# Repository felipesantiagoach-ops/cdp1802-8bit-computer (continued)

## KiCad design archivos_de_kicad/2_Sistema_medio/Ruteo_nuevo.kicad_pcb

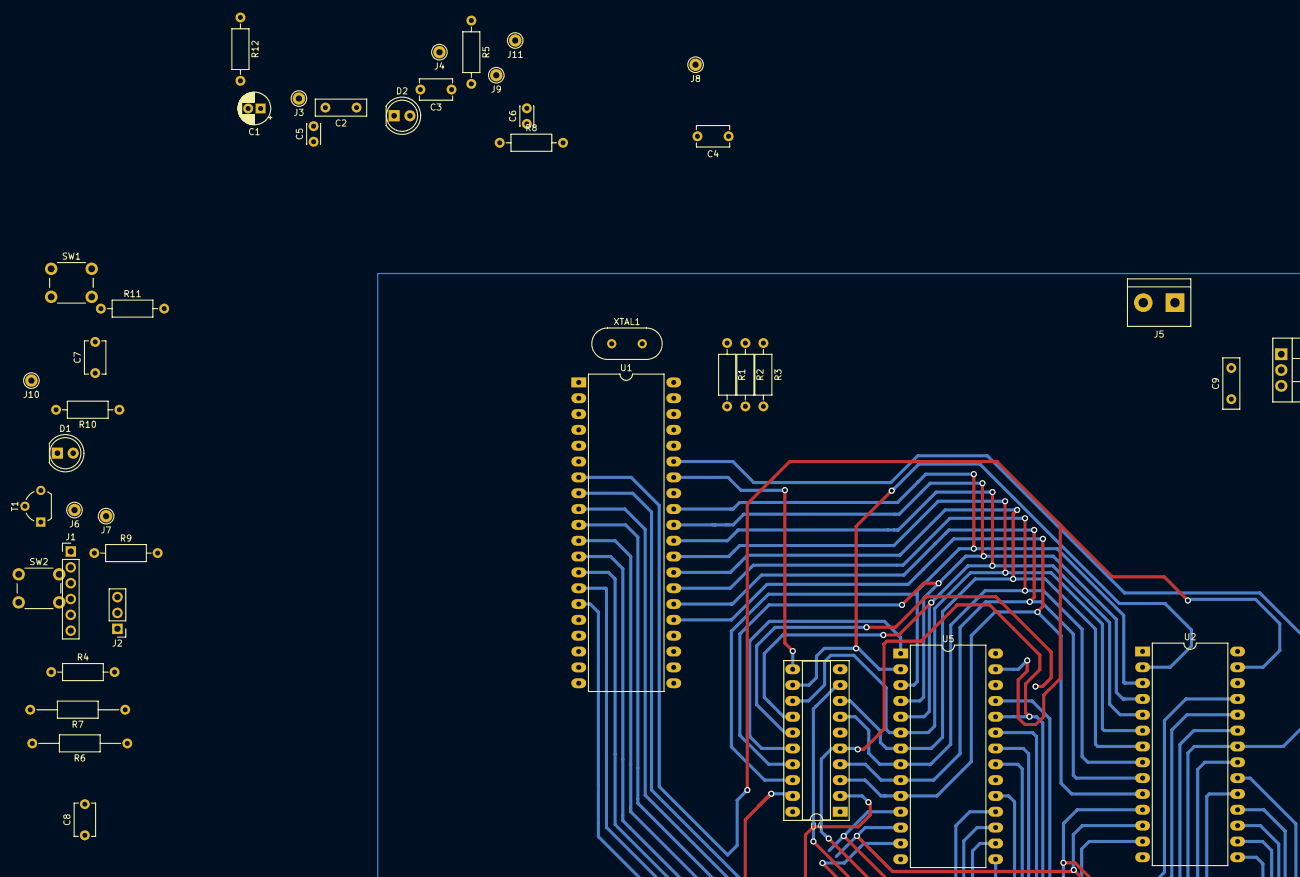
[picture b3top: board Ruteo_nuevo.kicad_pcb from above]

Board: 2 copper layers, 43 parts (0 on the bottom side), 50 nets.

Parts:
C1: 10uF; CP_Radial_D5.0mm_P2.00mm
C2, C9: 0,1uF; C_Disc_D8.0mm_W2.5mm_P5.00mm
C3, C4, C7, C8: 0,1uF; C_Disc_D5.1mm_W3.2mm_P5.00mm
C5, C6: 30pF; C_Disc_D3.0mm_W2.0mm_P2.50mm
D1, D2: LD271; LED_D5.0mm
J1: Conn_01x06_Male; PinHeader_1x06_P2.54mm_Vertical
J2: N1,2,3; PinHeader_1x03_P2.54mm_Vertical
J3, J4, J6, J7, J8: 1; Pin_D1.0mm_L10.0mm
J5: Voltaje de entrada; TerminalBlock_bornier-2_P5.08mm
J9: 2; Pin_D1.0mm_L10.0mm
J10: 3; Pin_D1.0mm_L10.0mm
J11: 4; Pin_D1.0mm_L10.0mm
R1, R2, R3: 47K; R_Axial_DIN0207_L6.3mm_D2.5mm_P10.16mm_Horizontal
R4, R11, R12: 47k; R_Axial_DIN0207_L6.3mm_D2.5mm_P10.16mm_Horizontal
R5, R9: 220; R_Axial_DIN0207_L6.3mm_D2.5mm_P10.16mm_Horizontal
R6, R7: 47K; R_Axial_DIN0207_L6.3mm_D2.5mm_P15.24mm_Horizontal
R8: 10M; R_Axial_DIN0207_L6.3mm_D2.5mm_P10.16mm_Horizontal
R10: 10K; R_Axial_DIN0207_L6.3mm_D2.5mm_P10.16mm_Horizontal
SW1, SW2: SW_Push; SW_PUSH_6mm_H4.3mm
T1: PN2222A; TO-92L_Wide
U1: CDP1802ACE; DIP-40_W15.24mm_LongPads
U2: EEPROM; DIP-28_W15.24mm_LongPads
U3: L7805; TO-220-3_Vertical
U4: 74LS373; DIP-20_W7.62mm_Socket_LongPads
U5: Dallas_RAM; DIP-28_W15.24mm_LongPads
XTAL1: 4 MHz; Crystal_HC18-U_Vertical

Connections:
A0: U1.25 (MA0), U2.10 (A0), U4.3 (D0), U5.10 (A0)
A1: U1.26 (MA1), U2.9 (A1), U4.4 (D1), U5.9 (A1)
A2: U1.27 (MA2), U2.8 (A2), U4.7 (D2), U5.8 (A2)
A3: U1.28 (MA3), U2.7 (A3), U4.8 (D3), U5.7 (A3)
A4: U1.29 (MA4), U2.6 (A4), U4.13 (D4), U5.6 (A4)
A5: U1.30 (MA5), U2.5 (A5), U4.14 (D5), U5.5 (A5)
A6: U1.31 (MA6), U2.4 (A6), U4.17 (D6), U5.4 (A6)
A7: U1.32 (MA7), U2.3 (A7), U4.18 (D7), U5.3 (A7)
A8: U2.25 (A8), U4.2 (O0), U5.25 (A8)
A9: U2.24 (A9), U4.5 (O1), U5.24 (A9)
A10: U2.21 (A10), U4.6 (O2), U5.21 (A10)
A11: U2.23 (A11), U4.9 (O3), U5.23 (A11)
A12: U2.2 (A12), U4.12 (O4), U5.2 (A12)
A13: U4.15 (O5), U5.26 (A13)
A14: U4.16 (O6), U5.1 (A14)
A15: U2.20 (~CS), U4.19 (O7)
CLEAR: C7.1, R11.2, SW1.2, U1.3 (~CLEAR)
CLOCK: C5.1, J9.1, R8.1, U1.1 (CLOCK), XTAL1.1
D0: U1.15 (BUS0), U2.11 (Q0), U5.11 (Q0)
D1: U1.14 (BUS1), U2.12 (Q1), U5.12 (Q1)
D2: U1.13 (BUS2), U2.13 (Q2), U5.13 (Q2)
D3: U1.12 (BUS3), U2.15 (Q3), U5.15 (Q3)
D4: U1.11 (BUS4), U2.16 (Q4), U5.16 (Q4)
D5: U1.10 (BUS5), U2.17 (Q5), U5.17 (Q5)
D6: U1.9 (BUS6), U2.18 (Q6), U5.18 (Q6)
D7: U1.8 (BUS7), U2.19 (Q7), U5.19 (Q7)
EF1: C8.1, R4.2, SW2.2, U1.24 (~EF1)
EF4: J1.4, U1.21 (~EF4)
GND: C1.2, C2.2, C3.2, C4.2, C5.2, C6.2, C7.2, C8.2, C9.2, D2.1 (K), J1.1, J3.1, J5.1, SW1.1, SW2.1, T1.1 (E), U1.20 (VSS), U2.14 (GND), U3.2 (GND), U4.1 (OE), U4.10 (GND), U5.14 (GND)
MRD: J11.1, U1.7 (~MRD), U2.27 (~WE), U5.27 (~WE)
MWR: U1.35 (~MWR), U2.22 (~OE), U5.22 (~OE)
N1: J2.1, U1.19 (N0)
N2: J2.2, U1.18 (N1)
N3: J2.3, U1.17 (N2)
unnamed: C1.1, C2.1, J5.2, U3.1 (IN)
unnamed: D1.1 (K), T1.3 (C)
unnamed: D1.2 (A), R9.2
unnamed: D2.2 (A), R5.2
unnamed: R1.2, U1.38 (~DMA_IN)
unnamed: R2.2, U1.37 (~DMA_OUT)
unnamed: R3.2, U1.36 (~INTERRUPT)
unnamed: R6.2, U1.23 (~EF2)
unnamed: R7.2, U1.22 (~EF3)
unnamed: R10.2, T1.2 (B)
Q: J1.5, J10.1, R10.1, U1.4 (Q)
TPA: J6.1, U1.34 (TPA), U4.11 (LE)
TPB: J7.1, U1.33 (TPB)
VCC: C3.1, C4.1, C9.1, J4.1, R1.1, R2.1, R3.1, R4.1, R5.1, R6.1, R7.1, R9.1, R11.1, R12.1, U1.16 (VCC), U1.40 (VDD), U2.28 (VCC), U3.3 (OUT), U4.20 (VCC), U5.28 (VCC)
WAIT: R12.2, U1.2 (~WAIT)
XTAL: C6.1, J8.1, R8.2, U1.39 (~XTAL), XTAL1.2
